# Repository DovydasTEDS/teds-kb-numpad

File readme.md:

# teds-kb-numpad

a numpad / 17-key keypad with per-key rgb lighting, qmk firmware and soon to be added via and possibly signalrgb support!

## links
[Journal](/JOURNAL.md) [Bill of Materials (markdown)](/bom.md)

## custom cool features
- custom 3d printed case
- cool looking pcb
- hotswap switch sockets
- per-key sk6812 mini-e lighting
- qmk firmware
- via (wip)
- signalrgb (wip)

## pcb design

made completely in kicad, with the TEDS logo and some small text stating the name.

## case design

i decided to make the case in 3 parts - the plate, the bottom, and then the top. 
it could be made with just the bottom and plate, but the top helps hide the screws and make it look nice.

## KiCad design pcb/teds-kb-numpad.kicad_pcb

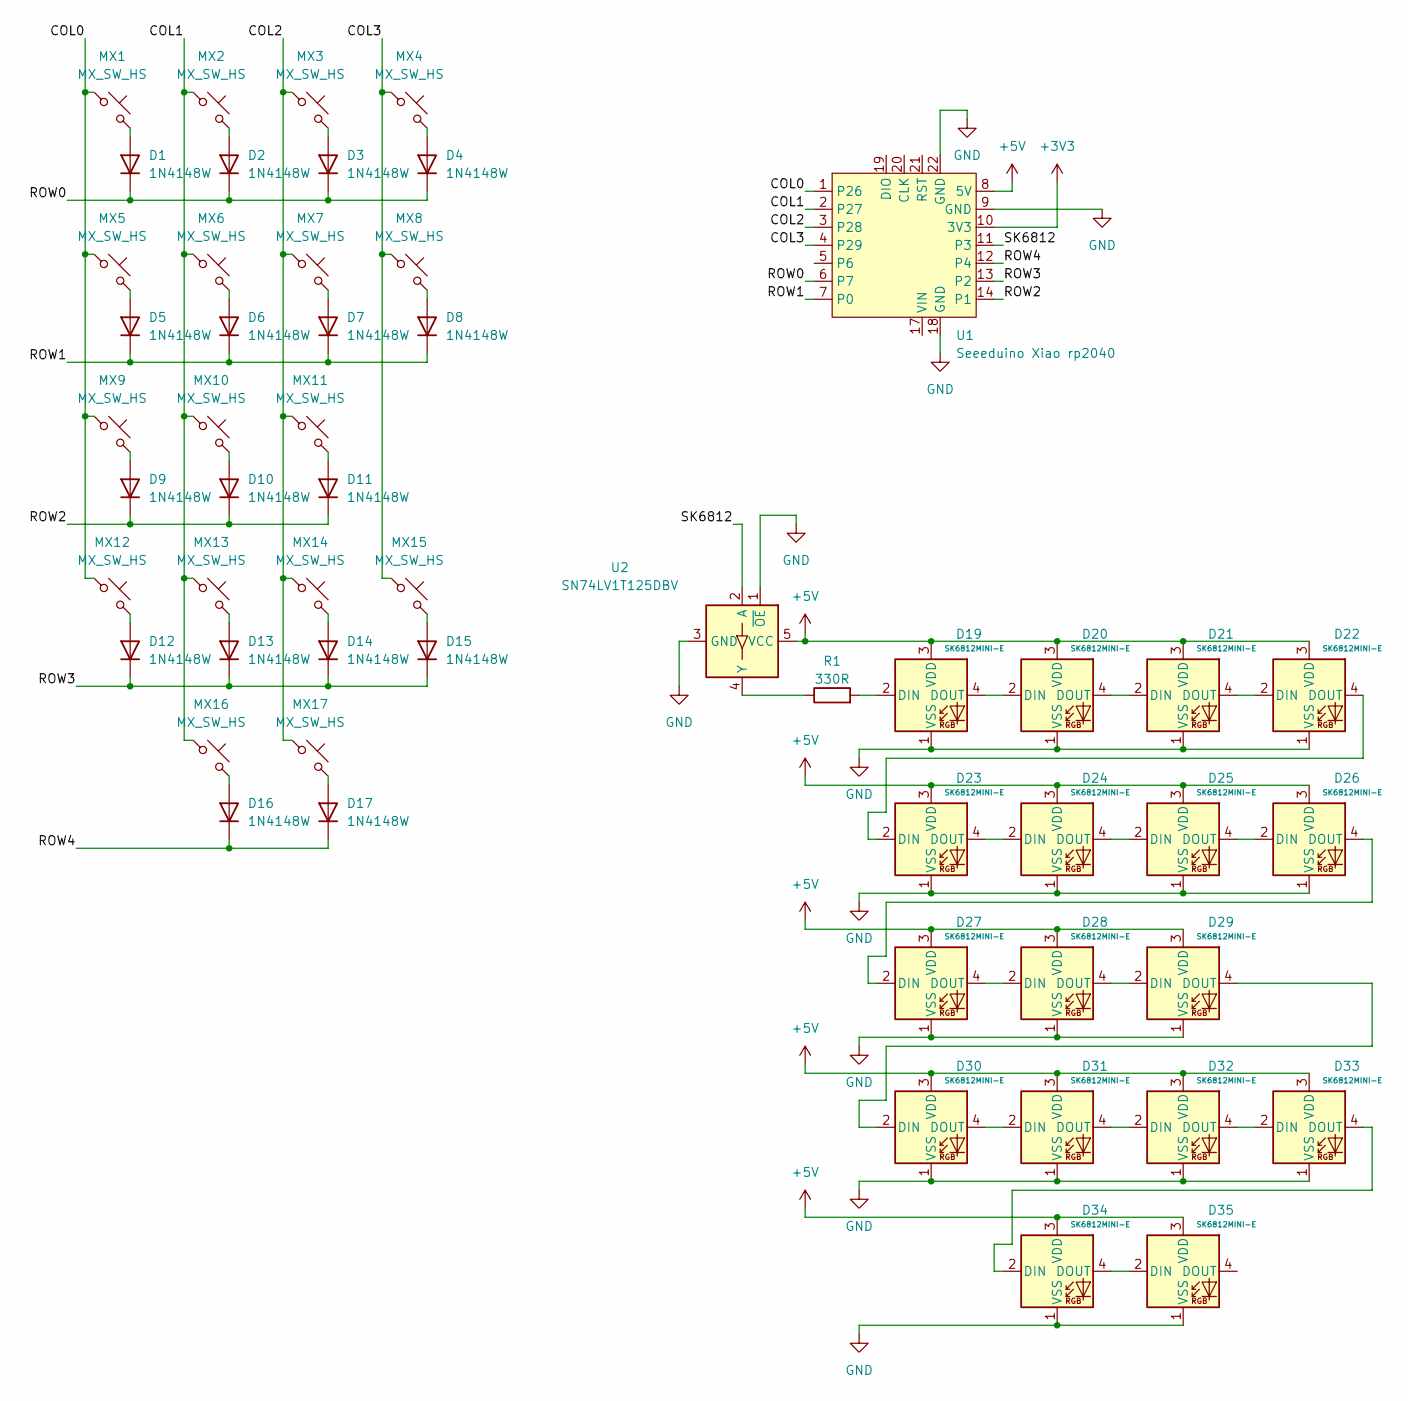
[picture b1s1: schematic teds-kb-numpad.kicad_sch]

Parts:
D1, D2, D3, D4, D5, D6, D7, D8, D9, D10, D11, D12, D13, D14, D15, D16, D17: 1N4148W; D_SOD-123
D19, D20, D21, D22, D23, D24, D25, D26, D27, D28, D29, D30, D31, D32, D33, D34, D35: SK6812MINI-E; LED_MX_6028R
MX1, MX2, MX3, MX4, MX5, MX6, MX7, MX8, MX9, MX10, MX11, MX12, MX13, MX14, MX15, MX16, MX17: MX_SW_HS; SW_MX_HS_CPG151101S11_1u
R1: 330R; R_0805_2012Metric_Pad1.20x1.40mm_HandSolder
U1: Seeeduino Xiao rp2040; Xiao_rp2040_ACH
U2: SN74LV1T125DBV; SOT-23-5_HandSoldering

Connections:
+3V3: U1.10 (3V3)
+5V: D19.3 (VDD), D20.3 (VDD), D21.3 (VDD), D22.3 (VDD), D23.3 (VDD), D24.3 (VDD), D25.3 (VDD), D26.3 (VDD), D27.3 (VDD), D28.3 (VDD), D29.3 (VDD), D30.3 (VDD), D31.3 (VDD), D32.3 (VDD), D33.3 (VDD), D34.3 (VDD), D35.3 (VDD), U1.8 (5V), U2.5 (VCC)
/COL0: MX1.1, MX5.1, MX9.1, MX12.1, U1.1 (P26)
/COL1: MX2.1, MX6.1, MX10.1, MX13.1, MX16.1, U1.2 (P27)
/COL2: MX3.1, MX7.1, MX11.1, MX14.1, MX17.1, U1.3 (P28)
/COL3: MX4.1, MX8.1, MX15.1, U1.4 (P29)
/ROW0: D1.1 (K), D2.1 (K), D3.1 (K), D4.1 (K), U1.6 (P7)
/ROW1: D5.1 (K), D6.1 (K), D7.1 (K), D8.1 (K), U1.7 (P0)
/ROW2: D9.1 (K), D10.1 (K), D11.1 (K), U1.14 (P1)
/ROW3: D12.1 (K), D13.1 (K), D14.1 (K), D15.1 (K), U1.13 (P2)
/ROW4: D16.1 (K), D17.1 (K), U1.12 (P4)
/SK6812: U1.11 (P3), U2.2 (A)
GND: D19.1 (VSS), D20.1 (VSS), D21.1 (VSS), D22.1 (VSS), D23.1 (VSS), D24.1 (VSS), D25.1 (VSS), D26.1 (VSS), D27.1 (VSS), D28.1 (VSS), D29.1 (VSS), D30.1 (VSS), D31.1 (VSS), D32.1 (VSS), D33.1 (VSS), D34.1 (VSS), D35.1 (VSS), U1.9 (GND), U1.18 (GND), U1.22 (GND), U2.1 (~OE), U2.3 (GND)
unnamed: D1.2 (A), MX1.2
unnamed: D2.2 (A), MX2.2
unnamed: D3.2 (A), MX3.2
unnamed: D4.2 (A), MX4.2
unnamed: D5.2 (A), MX5.2
unnamed: D6.2 (A), MX6.2
unnamed: D7.2 (A), MX7.2
unnamed: D8.2 (A), MX8.2
unnamed: D9.2 (A), MX9.2
unnamed: D10.2 (A), MX10.2
unnamed: D11.2 (A), MX11.2
unnamed: D12.2 (A), MX12.2
unnamed: D13.2 (A), MX13.2
unnamed: D14.2 (A), MX14.2
unnamed: D15.2 (A), MX15.2
unnamed: D16.2 (A), MX16.2
unnamed: D17.2 (A), MX17.2
unnamed: D19.2 (DIN), R1.2
unnamed: D19.4 (DOUT), D20.2 (DIN)
unnamed: D20.4 (DOUT), D21.2 (DIN)
unnamed: D21.4 (DOUT), D22.2 (DIN)
unnamed: D22.4 (DOUT), D23.2 (DIN)
unnamed: D23.4 (DOUT), D24.2 (DIN)
unnamed: D24.4 (DOUT), D25.2 (DIN)
unnamed: D25.4 (DOUT), D26.2 (DIN)
unnamed: D26.4 (DOUT), D27.2 (DIN)
unnamed: D27.4 (DOUT), D28.2 (DIN)
unnamed: D28.4 (DOUT), D29.2 (DIN)
unnamed: D29.4 (DOUT), D30.2 (DIN)
unnamed: D30.4 (DOUT), D31.2 (DIN)
unnamed: D31.4 (DOUT), D32.2 (DIN)
unnamed: D32.4 (DOUT), D33.2 (DIN)
unnamed: D33.4 (DOUT), D34.2 (DIN)
unnamed: D34.4 (DOUT), D35.2 (DIN)
unnamed: R1.1, U2.4 (Y)

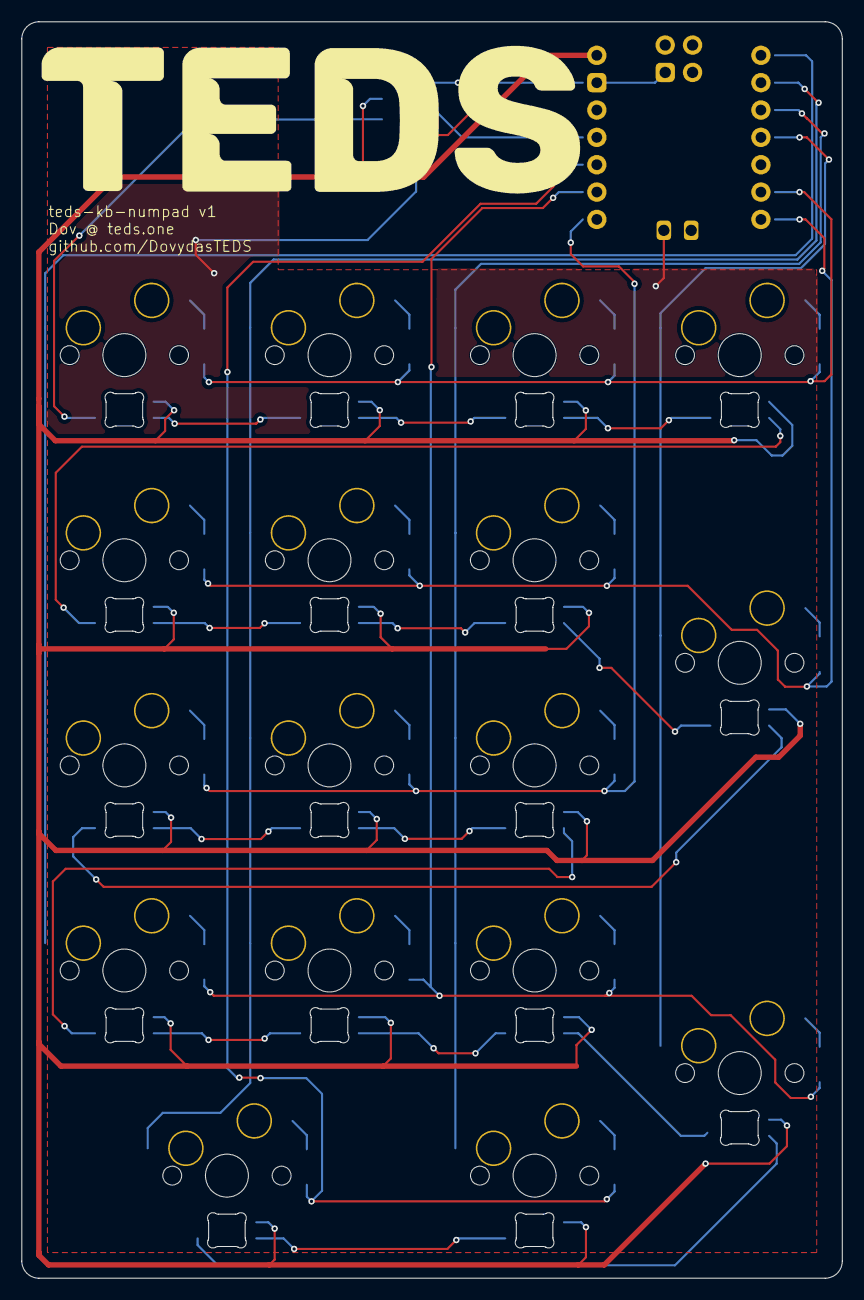
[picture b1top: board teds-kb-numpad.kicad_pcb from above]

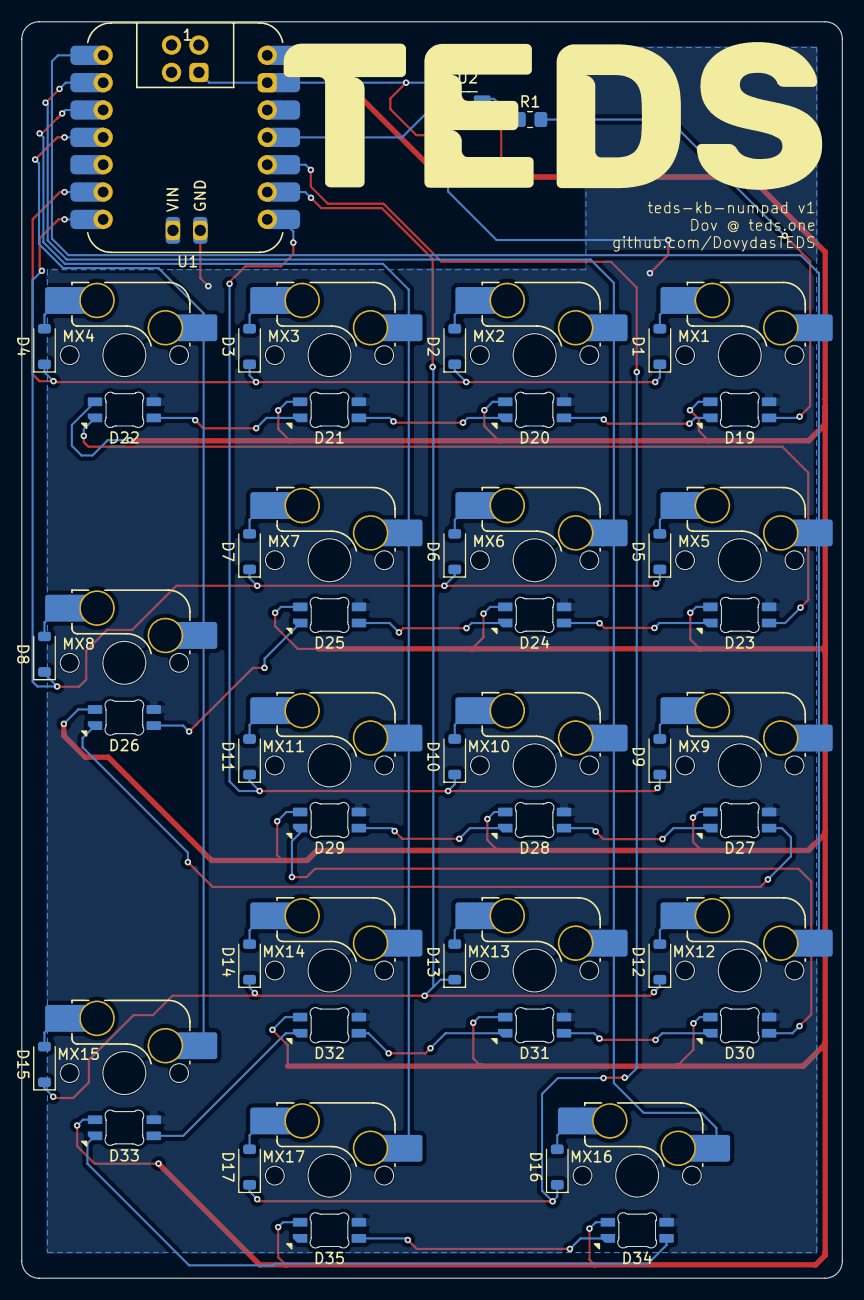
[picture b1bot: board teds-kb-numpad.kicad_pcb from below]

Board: 2 copper layers, 76.2 x 116.7 mm, 54 parts (54 on the bottom side), 47 nets.

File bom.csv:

Item,Link,LCSC Part No.,Price,Units,Total Price,Running Total,,Notes,,Specific No. Neded
PCB,,,12,1,12,12,,,,1
AliExpress,,,,,,12,,,,
Xiao RP2040,https://www.aliexpress.com/item/1005008233414789.html,,8.61,1,8.61,20.61,,,,1
Hotswap Socket,https://www.aliexpress.com/item/1005007232040760.html,,2.11,1,2.11,22.72,,,,17
Switches,https://www.aliexpress.com/item/1005005930656897.html,,15.41,1,15.41,38.13,,,,17
Stabilisers,https://www.aliexpress.com/item/1005006528731543.html,,0,1,0,38.13,,Already Owned,,3
Keycaps,https://www.aliexpress.com/item/1005009162201589.html,,10.34,1,10.34,48.47,,,,17
M3 8m Screw,https://www.aliexpress.com/item/1005007264845313.html,,0.81,1,0.81,49.28,,,,12
M3 Heatset OD4.2,https://www.aliexpress.com/item/1005003582355741.html,,0,1,0,49.28,,Already Owned,,12
LCSC,,,,,0,49.28,,,,
SK6812MINI-E,Already Owned,C5149201,0,17,0,49.28,,,,17
SN74LV1T125DBVR,Already Owned,C473338,0,1,0,49.28,,,,1
1N4148W,Already Owned,C917030,0,17,0,49.28,,,,17
0805W8F3300T5E,330 Resistor (Already Owned),C17630,0,1,0,49.28,,,,1
,,,,,0,49.28,,,,
Case,Self 3d Printed,,0,1,0,49.28,,,,1
,,,,,Total:,49.28,,,,
